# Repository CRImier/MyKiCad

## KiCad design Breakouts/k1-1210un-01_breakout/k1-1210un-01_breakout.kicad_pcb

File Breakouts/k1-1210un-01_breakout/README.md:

# K1-1210UN-01 switch breakout 

This is a small breakout for the K1-1210UN-01 five-direction SMD switch.
I made it so that it's easler to wire this switch in different configurations
while still retaining the small footprint.

This board is untested and there's no guarantees of fitness.

- PCB size: 12*12.5mm
- Layer count: 2

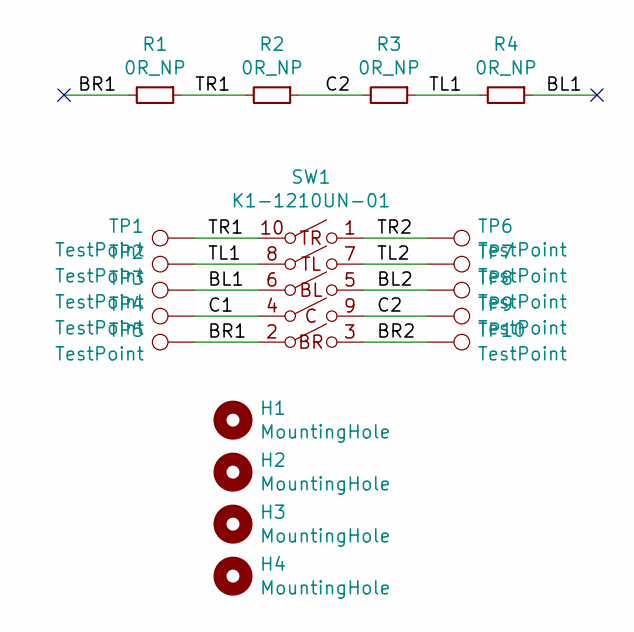
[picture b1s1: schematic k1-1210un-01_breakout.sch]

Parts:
H1, H2, H3, H4: MountingHole; PinHole_1,5mm
R1, R2, R3, R4: 0R_NP; R_0603_1608Metric
SW1: K1-1210UN-01
TP1, TP2, TP3, TP5, TP9: TestPoint; TestPoint_Pad_D1.0mm
TP4, TP6, TP7, TP8, TP10: TestPoint; TestPoint_Pad_D1.5mm

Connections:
/BL1: R4.1, SW1.6 (A), TP3.1
/BL2: SW1.5 (B), TP8.1
/BR1: R1.2, SW1.2 (A), TP5.1
/BR2: SW1.3 (B), TP10.1
/C1: SW1.4 (A), TP4.1
/C2: R2.1, R3.2, SW1.9 (B), TP9.1
/TL1: R3.1, R4.2, SW1.8 (A), TP2.1
/TL2: SW1.7 (B), TP7.1
/TR1: R1.1, R2.2, SW1.10 (A), TP1.1
/TR2: SW1.1 (B), TP6.1

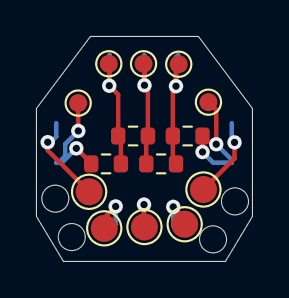
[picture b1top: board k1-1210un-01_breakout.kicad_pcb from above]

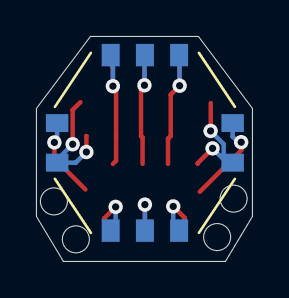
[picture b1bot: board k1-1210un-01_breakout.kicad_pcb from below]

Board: 2 copper layers, 12.0 x 12.5 mm, 19 parts (5 on the bottom side), 10 nets.

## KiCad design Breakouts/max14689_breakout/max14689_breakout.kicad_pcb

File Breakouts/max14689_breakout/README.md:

# MAX14689 BGA breakout

Small experimental breakout for the MAX14689 IC in BGA 0.4mm pitch package. Need to fix soldermask size around BGA pads before it's actually usable.

- PCB size: 10mm*8mm
- Layer count: 2

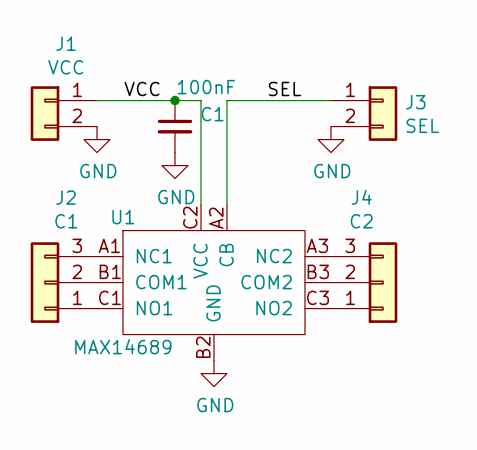
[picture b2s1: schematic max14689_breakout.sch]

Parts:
C1: 100nF; C_0402_1005Metric
J1: VCC; PinHeader_1x02_P2.00mm_Vertical
J2: C1; PinHeader_1x03_P2.00mm_Vertical
J3: SEL; PinHeader_1x02_P2.00mm_Vertical
J4: C2; PinHeader_1x03_P2.00mm_Vertical
U1: MAX14689; BGA-9_3x3_1.2x1.2mm

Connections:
/SEL: J3.1, U1.A2 (CB)
/VCC: C1.1, J1.1, U1.C2 (VCC)
GND: C1.2, J1.2, J3.2, U1.B2 (GND)
unnamed: J2.1, U1.C1 (NO1)
unnamed: J2.2, U1.B1 (COM1)
unnamed: J2.3, U1.A1 (NC1)
unnamed: J4.1, U1.C3 (NO2)
unnamed: J4.2, U1.B3 (COM2)
unnamed: J4.3, U1.A3 (NC2)

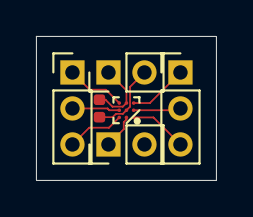
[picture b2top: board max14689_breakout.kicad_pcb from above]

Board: 2 copper layers, 10.0 x 8.0 mm, 6 parts (0 on the bottom side), 9 nets.

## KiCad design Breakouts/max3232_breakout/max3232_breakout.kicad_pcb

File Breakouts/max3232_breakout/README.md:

# Small MAX3232 breakout

A small breakout for MAX[3]232. Copies the format of Chinese MAX3232 breakout PCBs.
Capacitor values are specced for MAX3232, 3.3V operation. The PCB will work for MAX232
or other voltages but the cap values might have to be adjusted.

Signal names are silkscreened on the board, top and bottom layers.
This board is untested and there's no guarantees of fitness.

- PCB size: 8,6*17.5
- Layer count: 2
- Recommended thickness: t

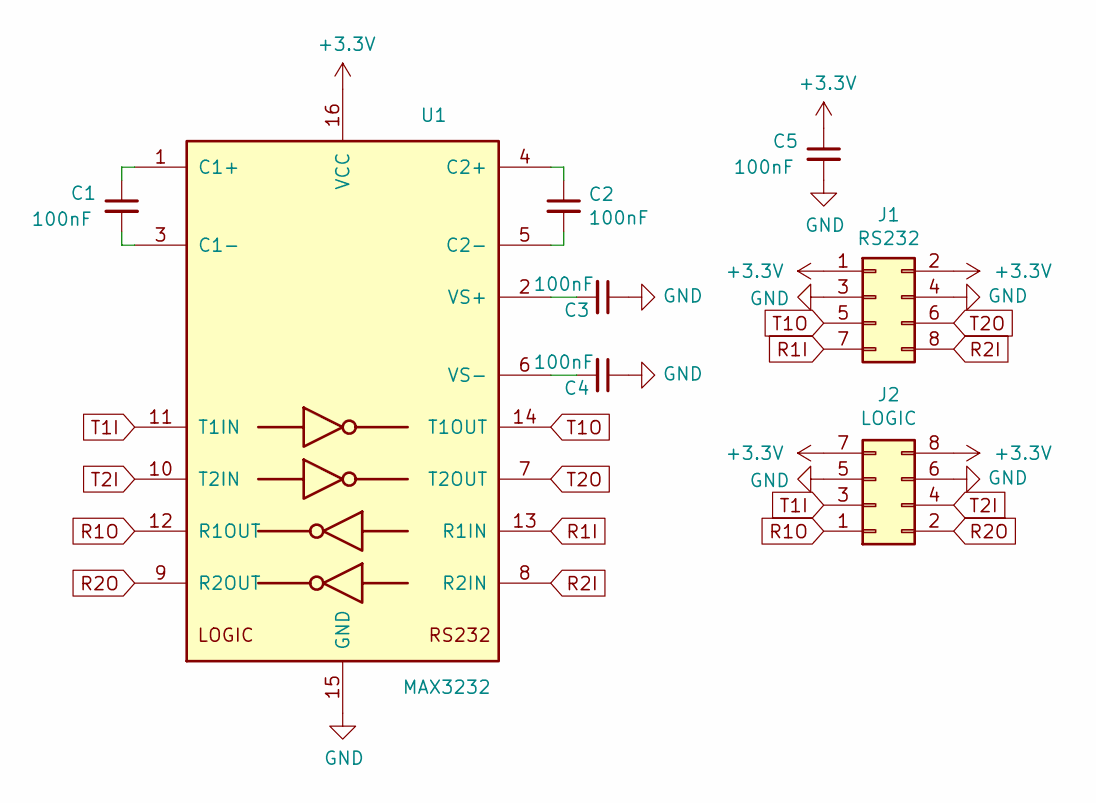
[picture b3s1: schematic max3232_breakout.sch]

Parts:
C1, C2, C3, C4, C5: 100nF; C_0805_2012Metric
J1: RS232; Side_2x4_Connector_SMD
J2: LOGIC; Side_2x4_Connector_SMD
U1: MAX3232; SOIC-16_3.9x9.9mm_P1.27mm

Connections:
+3V3: C5.1, J1.1, J1.2, J2.7, J2.8, U1.16 (VCC)
GND: C3.1, C4.1, C5.2, J1.3, J1.4, J2.5, J2.6, U1.15 (GND)
unnamed: C1.1, U1.1 (C1+)
unnamed: C1.2, U1.3 (C1-)
unnamed: C2.1, U1.4 (C2+)
unnamed: C2.2, U1.5 (C2-)
unnamed: C3.2, U1.2 (VS+)
unnamed: C4.2, U1.6 (VS-)
R1I: J1.7, U1.13 (R1IN)
R1O: J2.1, U1.12 (R1OUT)
R2I: J1.8, U1.8 (R2IN)
R2O: J2.2, U1.9 (R2OUT)
T1I: J2.3, U1.11 (T1IN)
T1O: J1.5, U1.14 (T1OUT)
T2I: J2.4, U1.10 (T2IN)
T2O: J1.6, U1.7 (T2OUT)

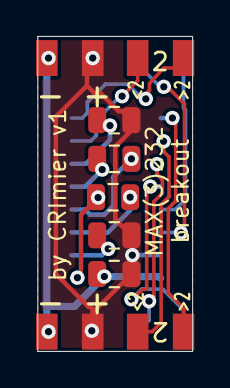
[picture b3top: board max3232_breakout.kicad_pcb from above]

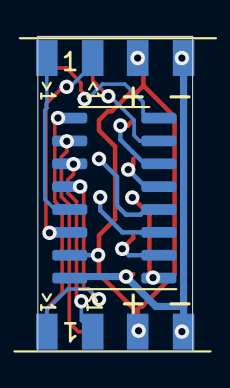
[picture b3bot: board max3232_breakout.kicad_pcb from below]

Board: 2 copper layers, 8.6 x 17.5 mm, 8 parts (3 on the bottom side), 16 nets.

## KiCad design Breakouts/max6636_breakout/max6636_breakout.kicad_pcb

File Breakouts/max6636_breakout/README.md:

# MAX6636 breakout

This is a breakout for the MAX6636 IC, which is a six-channel temperature sensor ADC connectable over I2C.
This breakout gives you access to all of the connections, including 6 pairs for temperature sensing.
On the back, the board has places for pullups on all of the IC's interface signals.

Temperature sensing pairs have + and - marked on the silkscreen, over the pins.
The I2C pinout is the default Raspberry Pi pinout - VCC-SDA-SCL-ALRT-GND.
The extra signals (OVERT and STBY) are available on an extra pin header and have an abbreviation silkscreened.

This board is untested and there's no guarantees of fitness.

- PCB size: 21x17mm
- Layer count: 2

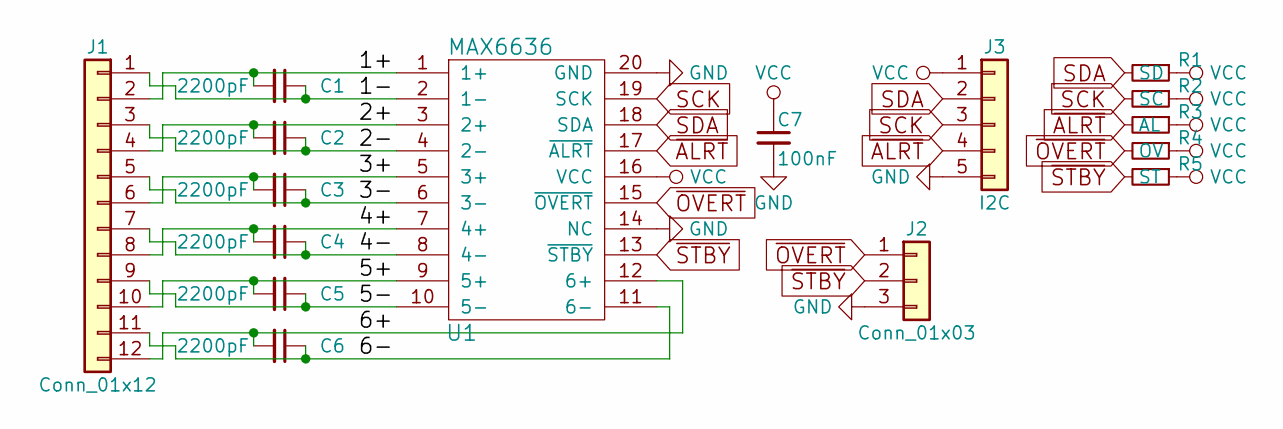
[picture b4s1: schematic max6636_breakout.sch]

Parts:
C1, C2, C3, C4, C5, C6: 2200pF; C_0603_HandSoldering
C7: 100nF; C_0603_HandSoldering
J1: Conn_01x12; Pin_Header_Straight_2x06_Pitch2.54mm
J2: Conn_01x03; Pin_Header_Straight_1x03_Pitch2.54mm
J3: I2C; Pin_Header_Straight_1x05_Pitch2.54mm
R1: SD; R_0603_HandSoldering
R2: SC; R_0603_HandSoldering
R3: AL; R_0603_HandSoldering
R4: OV; R_0603_HandSoldering
R5: ST; R_0603_HandSoldering
U1: MAX6636; TSSOP-20_4.4x6.5mm_Pitch0.65mm

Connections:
/1+: C1.2, J1.2, U1.1 (1+)
/1-: C1.1, J1.1, U1.2 (1-)
/2+: C2.2, J1.4, U1.3 (2+)
/2-: C2.1, J1.3, U1.4 (2-)
/3+: C3.2, J1.6, U1.5 (3+)
/3-: C3.1, J1.5, U1.6 (3-)
/4+: C4.2, J1.8, U1.7 (4+)
/4-: C4.1, J1.7, U1.8 (4-)
/5+: C5.2, J1.10, U1.9 (5+)
/5-: C5.1, J1.9, U1.10 (5-)
/6+: C6.2, J1.12, U1.12 (6+)
/6-: C6.1, J1.11, U1.11 (6-)
GND: C7.2, J2.3, J3.5, U1.14 (NC), U1.20 (GND)
SCK: J3.3, R2.2, U1.19 (SCK)
SDA: J3.2, R1.2, U1.18 (SDA)
VCC: C7.1, J3.1, R1.1, R2.1, R3.1, R4.1, R5.1, U1.16 (VCC)
~ALRT: J3.4, R3.2, U1.17 (~ALRT)
~OVERT: J2.1, R4.2, U1.15 (~OVERT)
~STBY: J2.2, R5.2, U1.13 (~STBY)

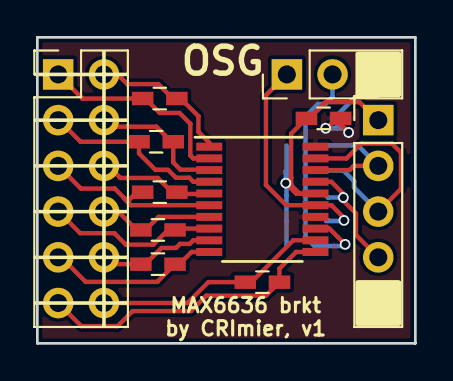
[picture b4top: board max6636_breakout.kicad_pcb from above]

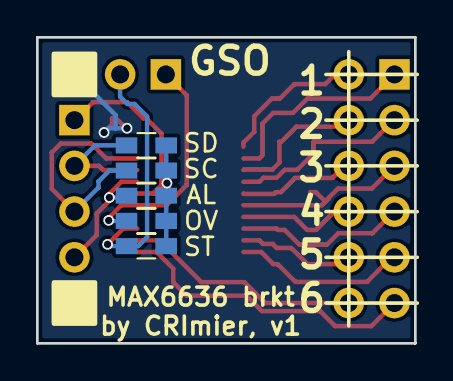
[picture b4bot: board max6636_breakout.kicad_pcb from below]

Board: 2 copper layers, 21.0 x 17.0 mm, 16 parts (5 on the bottom side), 19 nets.
